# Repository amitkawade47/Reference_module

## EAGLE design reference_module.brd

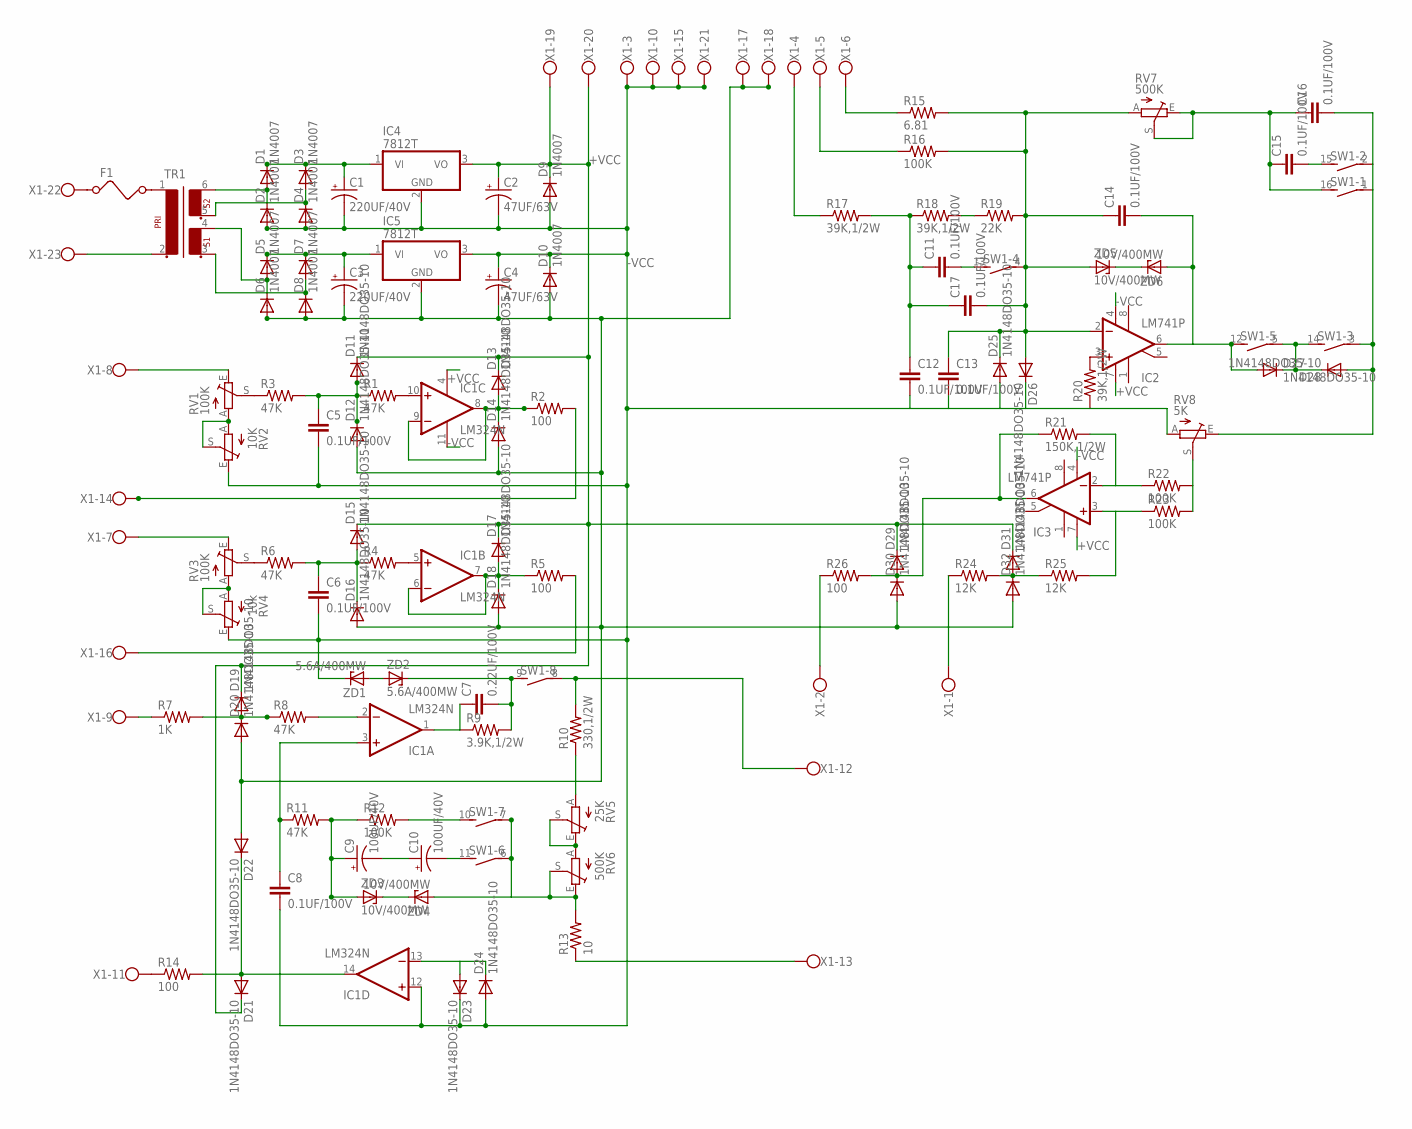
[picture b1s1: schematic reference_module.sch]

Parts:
C1, C3: 220UF/40V; E3,5-10
C2, C4: 47UF/63V; E3,5-10
C5, C6, C8, C11, C12, C13, C14, C15, C16, C17: 0.1UF/100V; C102-054X133
C7: 0.22UF/100V; C102-054X133
C9, C10: 100UF/40V; E3,5-10
D1, D2, D3, D4, D5, D6, D7, D8, D9, D10: 1N4007; DO41-10
D11, D12, D13, D14, D15, D16, D17, D18, D19, D20, D21, D22, D23, D24, D25, D26, D27, D28, D29, D30, D31, D32: 1N4148DO35-10; DO35-10
F1: FUSE
IC1: LM324N; DIL14
IC2, IC3: LM741P; DIL08
IC4, IC5: 7812T; TO220H
R1, R3, R4, R6, R8, R11: 47K; 0207/10
R2, R5, R14, R26: 100; 0207/10
R7: 1K; 0207/10
R9: 3.9K,1/2W; 0207/10
R10: 330,1/2W; 0207/10
R12, R16, R22, R23: 100K; 0207/10
R13: 10; 0207/10
R15: 6.81; 0207/10
R17, R18, R20: 39K,1/2W; 0207/10
R19: 22K; 0207/10
R21: 150K,1/2W; 0207/10
R24, R25: 12K; 0207/10
RV1, RV3: 100K; S63P
RV2: 10K; S63P
RV4: 10k; S63P
RV5: 25K; S63P
RV6, RV7: 500K; S63P
RV8: 5K; S63P
SW1: DIP08S
TR1: VR2230-2; VR22-2
X1: W237-6
ZD1, ZD2: 5.6A/400MW; ZDIO-10
ZD3, ZD4, ZD5, ZD6: 10V/400MW; ZDIO-10

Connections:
+VCC: C2.+, D9.C, D11.C, D13.C, D15.C, D17.C, D19.C, D21.C, D29.C, D31.C, IC1.4 (V+), IC2.7 (V+), IC3.7 (V+), IC4.3 (VO), X1.19, X1.20
-VCC: C1.-, C2.-, C4.+, C5.2, C6.2, C8.2, C12.2, C13.2, D2.A, D4.A, D9.A, D10.C, D23.C, D24.A, D25.A, D26.C, IC1.11 (V-), IC1.12 (+IN), IC2.4 (V-), IC3.4 (V-), IC4.2 (GND), IC5.3 (VO), R20.1, RV2.E, RV4.E, RV8.A, X1.3, X1.10, X1.15, X1.21, ZD1.C
unnamed: D1.A, D2.C, TR1.6
unnamed: D3.A, D4.C, TR1.5
unnamed: D5.A, D6.C, TR1.4
unnamed: D7.A, D8.C, TR1.3
unnamed: C1.+, D1.C, D3.C, IC4.1 (VI)
unnamed: RV1.A, RV2.A, RV2.S
unnamed: C3.+, D5.C, D7.C, IC5.1 (VI)
unnamed: RV3.A, RV4.A, RV4.S
unnamed: R7.1, X1.9
unnamed: RV1.E, X1.8
unnamed: R3.1, RV1.S
unnamed: C5.1, D11.A, D12.C, R1.1, R3.2
unnamed: F1.1, X1.22
unnamed: TR1.2, X1.23
unnamed: IC1.10 (+IN), R1.2
unnamed: D13.A, D14.C, IC1.8 (OUT), IC1.9 (-IN), R2.1
unnamed: R6.1, RV3.S
unnamed: C3.-, C4.-, D6.A, D8.A, D10.A, D12.A, D14.A, D16.A, D18.A, D20.A, D22.A, D30.A, D32.A, IC5.2 (GND), X1.17, X1.18
unnamed: R2.2, X1.14
unnamed: C6.1, D15.A, D16.C, R4.1, R6.2
unnamed: D19.A, D20.C, R7.2, R8.1
unnamed: IC1.5 (+IN), R4.2
unnamed: D17.A, D18.C, IC1.6 (-IN), IC1.7 (OUT), R5.1
unnamed: IC1.2 (-IN), R8.2
unnamed: RV3.E, X1.7
unnamed: R5.2, X1.16
unnamed: ZD1.A, ZD2.A
unnamed: C7.1, IC1.1 (OUT), R9.1
unnamed: C7.2, R9.2, SW1.9 (2), ZD2.C
unnamed: R10.2, SW1.8 (1), X1.12
unnamed: R10.1, RV5.A
unnamed: RV5.E, RV5.S, RV6.A
unnamed: C9.+, R11.2, R12.1, ZD3.A
unnamed: R14.1, X1.11
unnamed: C8.1, IC1.3 (+IN), R11.1
unnamed: R12.2, SW1.10 (2)
unnamed: C9.-, C10.+
unnamed: C10.-, SW1.11 (2)
unnamed: R13.2, RV6.E, RV6.S, SW1.6 (1), SW1.7 (1), ZD4.A
unnamed: ZD3.C, ZD4.C
unnamed: D23.A, D24.C, IC1.13 (-IN)
unnamed: D21.A, D22.C, IC1.14 (OUT), R14.2
unnamed: R13.1, X1.13
unnamed: IC2.3 (+IN), R20.2
unnamed: C15.2, SW1.15 (2)
unnamed: C11.1, C12.1, C17.1, R17.2, R18.1
unnamed: C11.2, SW1.13 (2)
unnamed: R18.2, R19.1
unnamed: R15.1, X1.6
unnamed: R16.1, X1.5
unnamed: R17.1, X1.4
unnamed: C13.1, C14.1, C17.2, D25.C, D26.A, IC2.2 (-IN), R15.2, R16.2, R19.2, RV7.A, SW1.4 (1), ZD5.A
unnamed: C15.1, C16.1, RV7.E, RV7.S, SW1.16 (2)
unnamed: D27.C, D28.C, SW1.5 (1), SW1.14 (2)
unnamed: F1.2, TR1.1
unnamed: C14.2, D27.A, IC2.6 (OUT), SW1.12 (2), ZD6.A
unnamed: ZD5.C, ZD6.C
unnamed: R22.2, R23.2, RV8.S
unnamed: IC3.2 (-IN), R21.2, R22.1
unnamed: IC3.3 (+IN), R23.1, R25.2
unnamed: D29.A, D30.C, IC3.6 (OUT), R21.1, R26.2
unnamed: D31.A, D32.C, R24.2, R25.1
unnamed: R26.1, X1.2
unnamed: R24.1, X1.1
unnamed: C16.2, D28.A, RV8.E, SW1.1, SW1.2 (1), SW1.3 (1)

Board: 2 copper layers, 98 parts (0 on the bottom side), 67 nets, no tracks yet.

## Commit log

2018-03-15 schematic
    polarised capacitor direction remained.
    other part of schematic is done.
2018-03-17 Board file
    Component placing done.
2018-03-21 diptrace
    schematic and pcb layout is imported in diptrace.
2018-03-22 schematic and PCB
    changed D26 connection
    added +vcc and -vcc to IC
    schematic verified.
    PCB layout done in diptrace.
2018-03-22 PDF
    comppnent side ,top side, bottom side pdf added
2018-03-22 PCB layout edit
    edited tracks in top and bottom side
